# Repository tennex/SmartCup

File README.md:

# SmartCup
Hardware project

Readme: http://digi.physic.ut.ee/rvp/index.php/Kasutaja:Sander.Orav#Tark_tass

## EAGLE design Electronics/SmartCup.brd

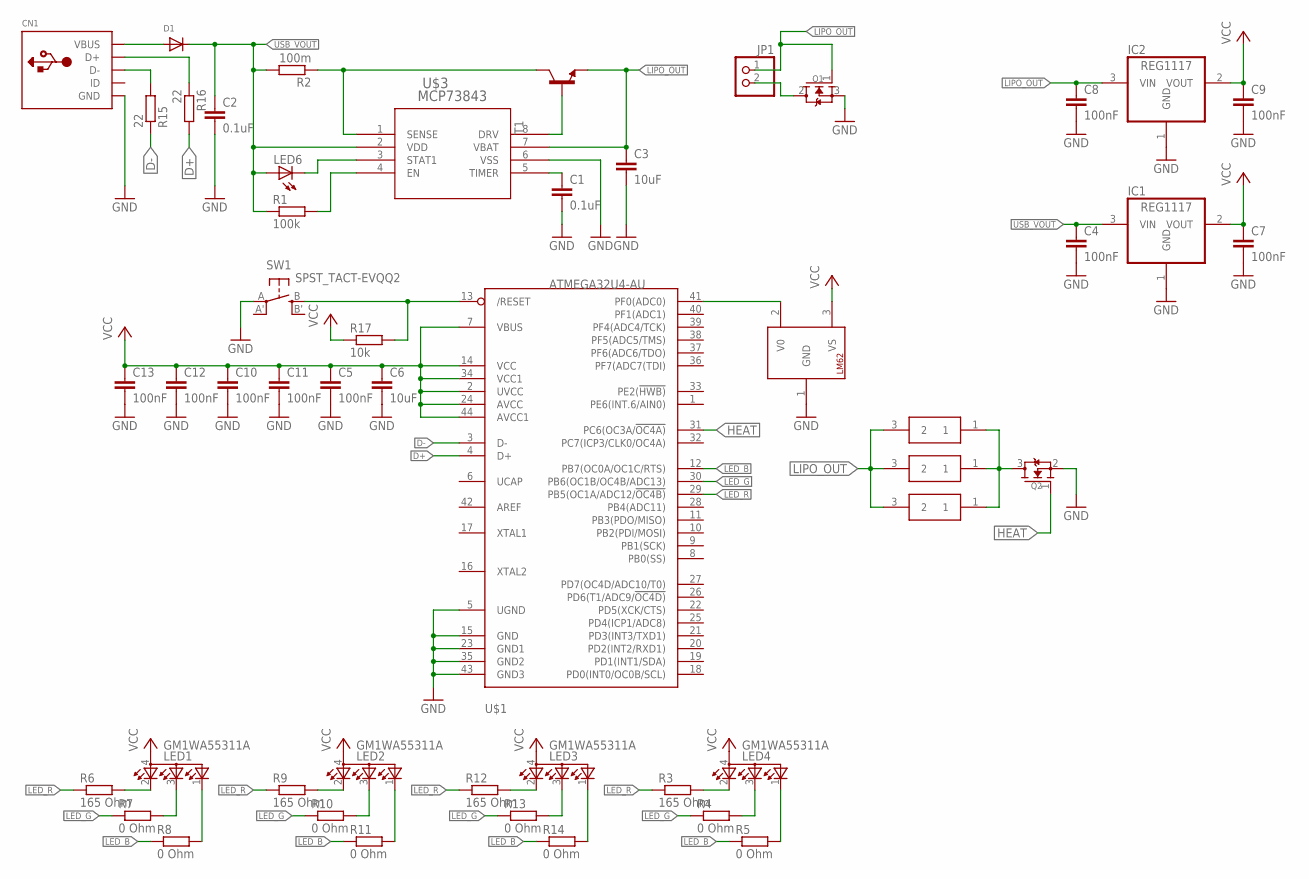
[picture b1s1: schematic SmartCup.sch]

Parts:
C1, C2: 0.1uF; C0603
C3: 10uF; C0603
C4, C5, C7, C8, C9, C10, C11, C12, C13: 100nF; C0603
C6: 10uF; C0805
CN1: USBMINIB; USB-MINIB
D1: DIODE_SOD-123FL; SOD-123FL
IC1, IC2: REG1117; SOT223
JP1: PINHD-1X2; 1X02
LED1, LED2, LED3, LED4: GM1WA55311A
LED6: LEDCHIP-LED0603; CHIP-LED0603
Q1: MOSFET-NSOT223; SOT223
Q2: MOSFET-NREFLOW; SOT23
R1: 100k; R0603
R2: 100m; R0603
R3, R6, R9, R12: 165 Ohm; R0603
R4, R5, R7, R8, R10, R11, R13, R14: 0 Ohm; R0603
R15, R16: 22; R0603
R17: 10k; R0603
SW1: SPST_TACT-EVQQ2; EVQ-Q2
T1: -NPN-SOT23-EBC; SOT23-EBC
U$1: ATMEGA32U4-AU; TQFP44
U$3: MCP73843; MSOP8_MC
U$4: LM62TO-92; TO92-
U$6, U$7, U$8: BOURNS_PWR; DPAK

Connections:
D+: R16.2, U$1.4 (D+)
D-: R15.1, U$1.3 (D-)
GND: C1.2, C2.2, C3.2, C4.2, C5.2, C6.2, C7.2, C8.2, C9.2, C10.2, C11.2, C12.2, C13.2, CN1.GND, IC1.1 (GND), IC2.1 (GND), Q1.3 (S), Q2.2 (S), SW1.A, U$1.5 (UGND), U$1.15 (GND), U$1.23 (GND1), U$1.35 (GND2), U$1.43 (GND3), U$3.6 (VSS), U$4.1 (GND)
HEAT: Q2.1 (G), U$1.31 (PC6(OC3A/!OC4A))
LED_B: R5.1, R8.1, R11.1, R14.1, U$1.12 (PB7(OC0A/OC1C/RTS))
LED_G: R4.1, R7.1, R10.1, R13.1, U$1.30 (PB6(OC1B/OC4B/ADC13))
LED_R: R3.1, R6.1, R9.1, R12.1, U$1.29 (PB5(OC1A/ADC12/!OC4B))
LIPO_OUT: C3.1, C8.1, IC2.3 (VIN), JP1.1, Q1.1 (G), T1.E, U$3.7 (VBAT), U$6.3 (2), U$7.3 (2), U$8.3 (2)
unnamed: LED6.C, U$3.3 (STAT1)
unnamed: CN1.VBUS, D1.A
unnamed: R1.2, U$3.4 (EN)
unnamed: T1.B, U$3.8 (DRV)
unnamed: C1.1, U$3.5 (TIMER)
unnamed: LED4.2 (CRED), R3.2
unnamed: JP1.2, Q1.2 (D)
unnamed: LED3.2 (CRED), R12.2
unnamed: LED4.3 (CBLUE), R4.2
unnamed: R2.1, T1.C, U$3.1 (SENSE)
unnamed: LED4.1 (CGREEN), R5.2
unnamed: LED1.2 (CRED), R6.2
unnamed: LED1.3 (CBLUE), R7.2
unnamed: LED1.1 (CGREEN), R8.2
unnamed: LED2.2 (CRED), R9.2
unnamed: LED2.3 (CBLUE), R10.2
unnamed: LED2.1 (CGREEN), R11.2
unnamed: LED3.3 (CBLUE), R13.2
unnamed: LED3.1 (CGREEN), R14.2
unnamed: U$1.41 (PF0(ADC0)), U$4.2 (V0)
unnamed: CN1.D-, R15.2
unnamed: CN1.D+, R16.1
unnamed: R17.2, SW1.B (S), U$1.13 (/RESET)
unnamed: Q2.3 (D), U$6.1, U$7.1, U$8.1
USB_VOUT: C2.1, C4.1, D1.C, IC1.3 (VIN), LED6.A, R1.1, R2.2, U$3.2 (VDD)
VCC: C5.1, C6.1, C7.1, C9.1, C10.1, C11.1, C12.1, C13.1, IC1.2 (VOUT), IC2.2 (VOUT), LED1.4 (A), LED2.4 (A), LED3.4 (A), LED4.4 (A), R17.1, U$1.2 (UVCC), U$1.7 (VBUS), U$1.14 (VCC), U$1.24 (AVCC), U$1.34 (VCC1), U$1.44 (AVCC1), U$4.3 (VS)

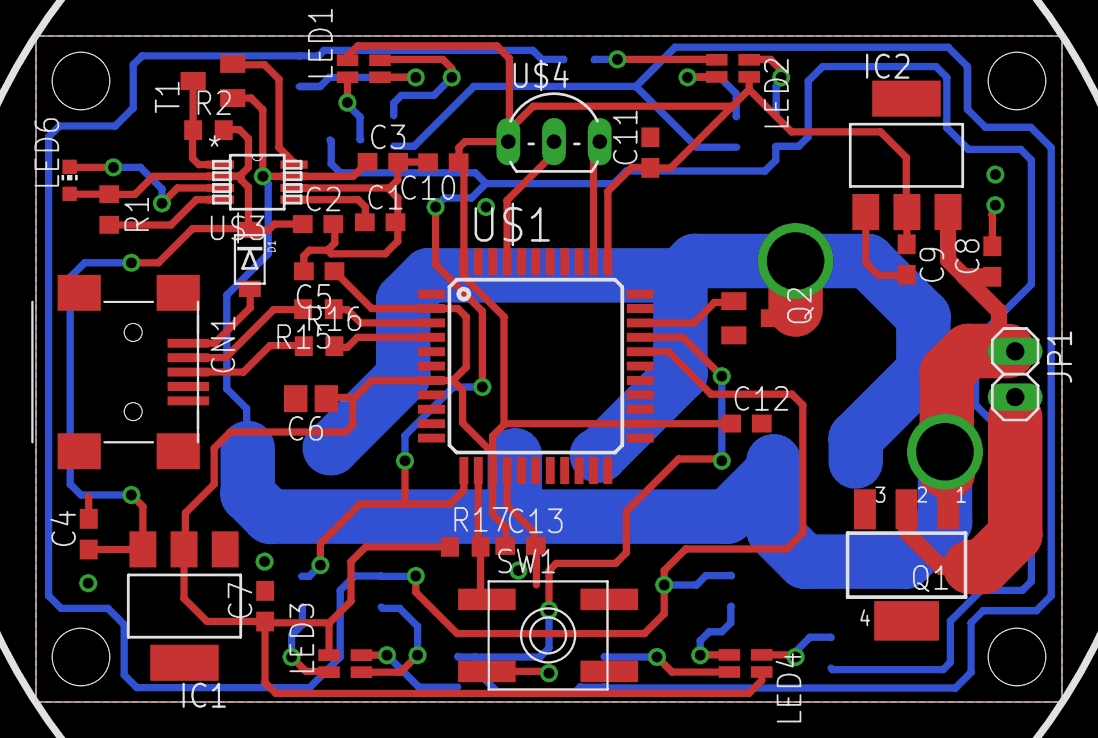
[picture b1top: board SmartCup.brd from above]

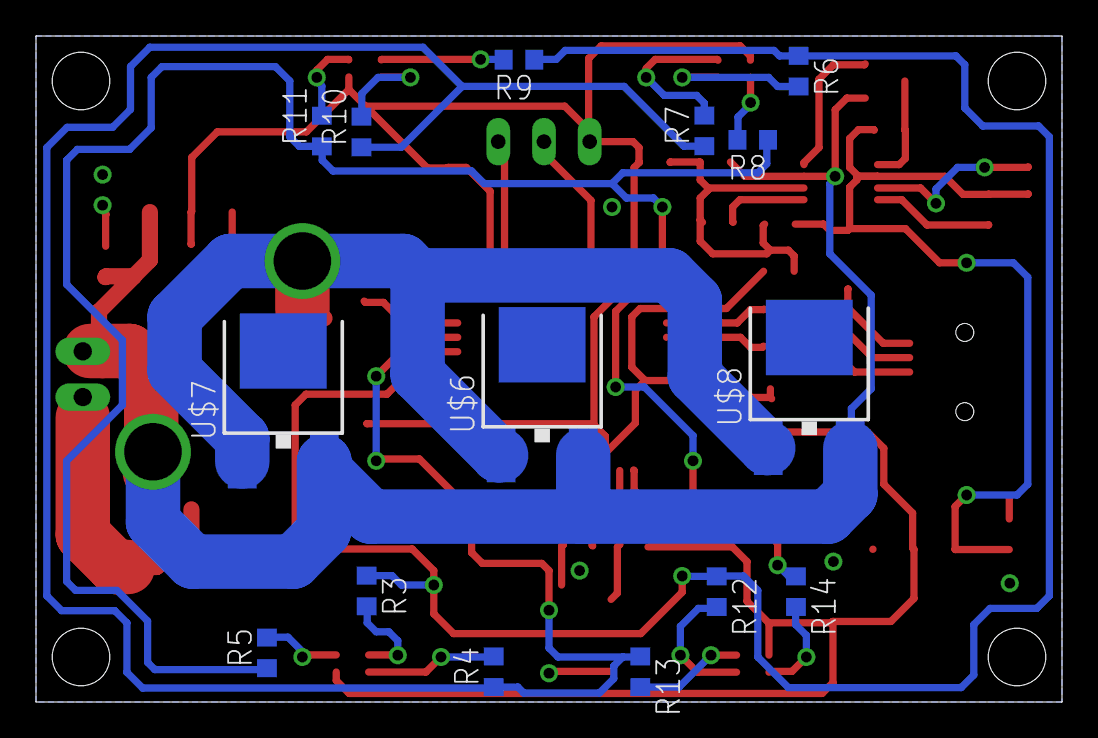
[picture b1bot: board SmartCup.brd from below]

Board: 2 copper layers, 57.0 x 37.0 mm, 50 parts (15 on the bottom side), 34 nets.

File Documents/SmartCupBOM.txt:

Partlist exported from C:/Users/Orav/Desktop/SmartCup/SmartCup.sch at 27.11.2014 10:28:52

Part Value           Device          Package      Description                                       MF MPN     OC_FARNELL OC_NEWARK
+	C1   0.1uF           C-EUC0603       C0603        CAPACITOR, European symbol                                                       
+	C2   0.1uF           C-EUC0603       C0603        CAPACITOR, European symbol                                                       
+	C3   10uF            C-EUC0603       C0603        CAPACITOR, European symbol                                                       
+	C4   100nF           C-EUC0603       C0603        CAPACITOR, European symbol                                                       
+	C5   100nF           C-EUC0603       C0603        CAPACITOR, European symbol                                                       
+	C6   10uF            C-EUC0805       C0805        CAPACITOR, European symbol                                                       
+	C7   100nF           C-EUC0603       C0603        CAPACITOR, European symbol                                                       
+	C8   100nF           C-EUC0603       C0603        CAPACITOR, European symbol                                                       
+	C9   100nF           C-EUC0603       C0603        CAPACITOR, European symbol                                                       
+	C10  100nF           C-EUC0603       C0603        CAPACITOR, European symbol                                                       
+	C11  100nF           C-EUC0603       C0603        CAPACITOR, European symbol                                                       
+	C12  100nF           C-EUC0603       C0603        CAPACITOR, European symbol                                                       
+	C13  100nF           C-EUC0603       C0603        CAPACITOR, European symbol                                                       
+	CN1                  USBMINIB        USB-MINIB    USB Connectors                                                                   
+	D1                   DIODE_SOD-123FL SOD-123FL    Diode                                                                            
+	IC1  REG1117         REG1117         SOT223       800mA and 1A Low Dropout (LDO) Positive Regulator    REG1117 	1097566    14P6981  
+	IC2  REG1117         REG1117         SOT223       800mA and 1A Low Dropout (LDO) Positive Regulator    REG1117 	1097566    14P6981  
JP1                  PINHD-1X2       1X02         PIN HEADER                                                                       
+	LED1 GM1WA55311A     GM1WA55311A     GM1WA55311A  Chip LED RGB                                                                     
+	LED2 GM1WA55311A     GM1WA55311A     GM1WA55311A  Chip LED RGB                                                                     
+	LED3 GM1WA55311A     GM1WA55311A     GM1WA55311A  Chip LED RGB                                                                     
+	LED4 GM1WA55311A     GM1WA55311A     GM1WA55311A  Chip LED RGB                                                                     
+	LED6                 LEDCHIP-LED0603 CHIP-LED0603 LED                                                                              
+	Q1                   MOSFET-NSOT223  SOT223       N-Channel Mosfet                                                                 
+	Q2                   MOSFET-NREFLOW  SOT23        N-Channel Mosfet                                                                 
+	R1   100k            R-EU_R0603      R0603        RESISTOR, European symbol                                                        
+	R2   100m            R-EU_R0603      R0603        RESISTOR, European symbol                                                        
+	R3   165 Ohm         R-EU_R0603      R0603        RESISTOR, European symbol                                                        
+	R4   0 Ohm           R-EU_R0603      R0603        RESISTOR, European symbol                                                        
+	R5   0 Ohm           R-EU_R0603      R0603        RESISTOR, European symbol                                                        
+	R6   165 Ohm         R-EU_R0603      R0603        RESISTOR, European symbol                                                        
+	R7   0 Ohm           R-EU_R0603      R0603        RESISTOR, European symbol                                                        
+	R8   0 Ohm           R-EU_R0603      R0603        RESISTOR, European symbol                                                        
+	R9   165 Ohm         R-EU_R0603      R0603        RESISTOR, European symbol                                                        
+	R10  0 Ohm           R-EU_R0603      R0603        RESISTOR, European symbol                                                        
+	R11  0 Ohm           R-EU_R0603      R0603        RESISTOR, European symbol                                                        
+	R12  165 Ohm         R-EU_R0603      R0603        RESISTOR, European symbol                                                        
+	R13  0 Ohm           R-EU_R0603      R0603        RESISTOR, European symbol                                                        
+	R14  0 Ohm           R-EU_R0603      R0603        RESISTOR, European symbol                                                        
+	R15  22              R-EU_R0603      R0603        RESISTOR, European symbol                                                        
+	R16  22              R-EU_R0603      R0603        RESISTOR, European symbol                                                        
+	R17  10k             R-EU_R0603      R0603        RESISTOR, European symbol                                                        
+	SW1  SPST_TACT-EVQQ2 SPST_TACT-EVQQ2 EVQ-Q2       SMT 6mm switch, EVQQ2 series                                                     
+	T1                   -NPN-SOT23-EBC  SOT23-EBC    NPN Transistror                                                                  
+	U$1  ATMEGA32U4-AU   ATMEGA32U4-AU   TQFP44       http://www.ladyada.net/library/eagle                                             
+	U$3  MCP73843        MCP73843        MSOP8_MC                                                                                      
+	U$4  LM62TO-92       LM62TO-92       TO92-                                                                                         
+	U$6  BOURNS_PWR      BOURNS_PWR      DPAK                                                                                          
+	U$7  BOURNS_PWR      BOURNS_PWR      DPAK                                                                                          
+	U$8  BOURNS_PWR      BOURNS_PWR      DPAK

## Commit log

2014-11-17 First commit: - Model - Schematic and board
2014-11-21 Board update
2015-02-16 SolidWorks model
2015-02-16 Cleanup - removed unnecessary files.
2015-02-27 Software
